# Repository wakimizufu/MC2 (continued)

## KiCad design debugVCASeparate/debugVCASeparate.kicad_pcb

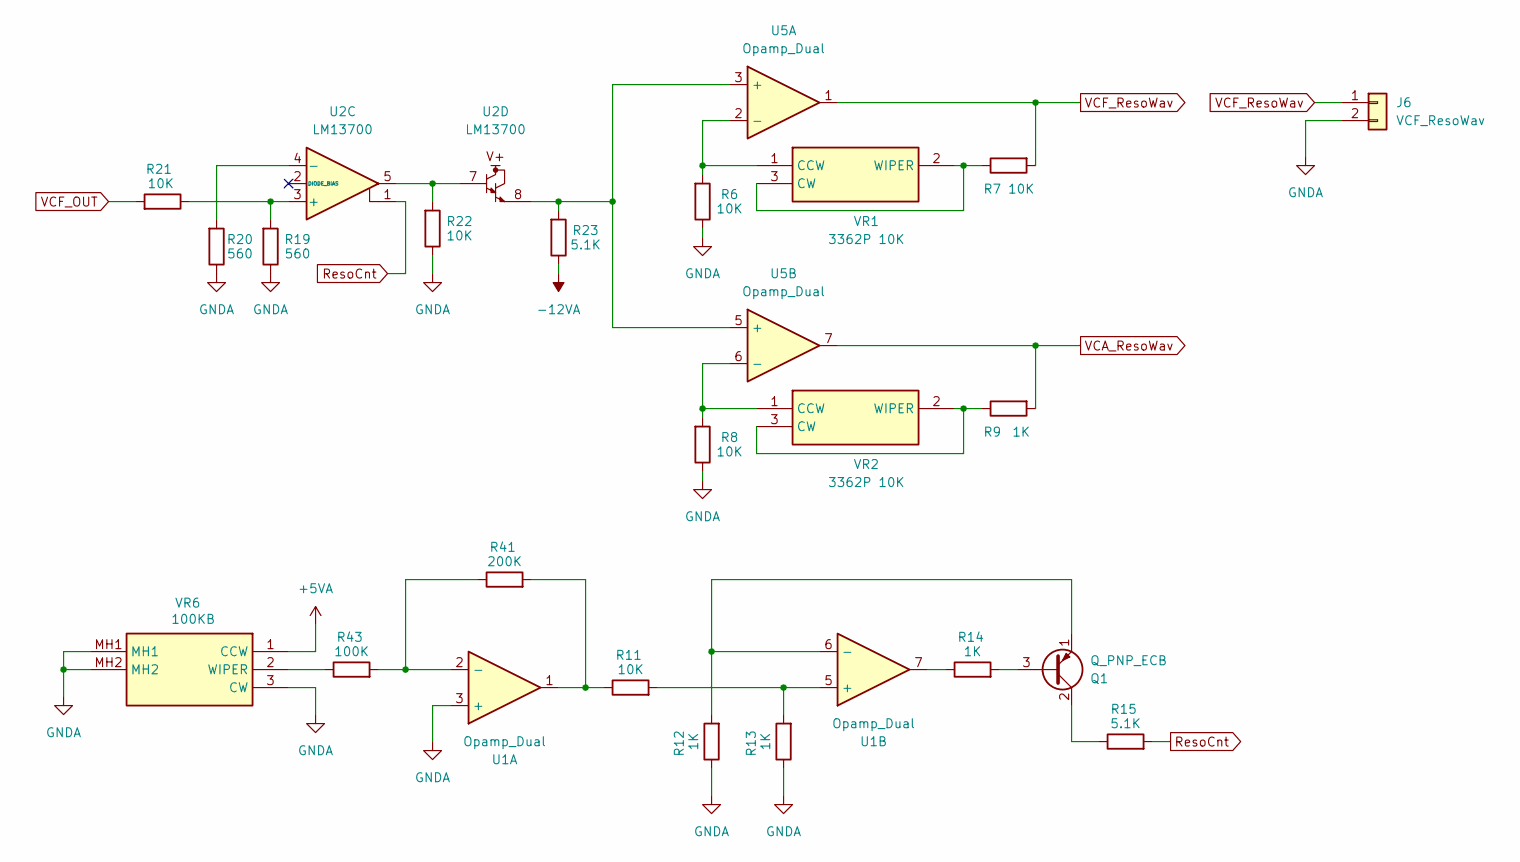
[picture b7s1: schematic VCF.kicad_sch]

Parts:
J6: VCF_ResoWav; PinSocket_1x02_P2.54mm_Vertical
Q1: Q_PNP_ECB; TO-92_HandSolder
R6, R7, R8, R11, R21, R22: 10K; R_Axial_DIN0204_L3.6mm_D1.6mm_P7.62mm_Horizontal
R9, R12, R13, R14: 1K; R_Axial_DIN0204_L3.6mm_D1.6mm_P7.62mm_Horizontal
R15, R23: 5.1K; R_Axial_DIN0204_L3.6mm_D1.6mm_P7.62mm_Horizontal
R19, R20: 560; R_Axial_DIN0204_L3.6mm_D1.6mm_P7.62mm_Horizontal
R41: 200K; R_Axial_DIN0204_L3.6mm_D1.6mm_P7.62mm_Horizontal
R43: 100K; R_Axial_DIN0204_L3.6mm_D1.6mm_P7.62mm_Horizontal
U1: Opamp_Dual; DIP-8_W7.62mm_LongPads
U2: LM13700; DIP-16_W7.62mm_LongPads
U5: Opamp_Dual; DIP-8_W7.62mm_Socket_LongPads
VR1, VR2: 3362P 10K; 3362P_1; Manufacturer_Part_Number 3362P-1-103LF; Mouser Part Number 652-3362P-1-103LF
VR6: 100KB; RK09D117000B; Manufacturer_Part_Number RK09D117000B; Mouser Part Number 688-RK09D117000B

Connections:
+5VA: VR6.1 (CCW); also elsewhere on the board
-12VA: R23.1; also elsewhere on the board
GNDA: J6.2, R6.1, R8.1, R12.1, R13.1, R19.1, R20.1, R22.1, U1.3 (+), VR6.3 (CW), VR6.MH1, VR6.MH2; also elsewhere on the board
unnamed: Q1.3 (B), R14.2
unnamed: Q1.2 (C), R15.1
unnamed: Q1.1 (E), R12.2, U1.6 (-)
unnamed: R11.1, R41.2, U1.1
unnamed: R14.1, U1.7
unnamed: R22.2, U2.5, U2.7
unnamed: R41.1, R43.2, U1.2 (-)
unnamed: R11.2, R13.2, U1.5 (+)
unnamed: R19.2, R21.1, U2.3 (+)
unnamed: R20.2, U2.4 (-)
unnamed: R23.2, U2.8, U5.3 (+), U5.5 (+)
unnamed: R6.2, U5.2 (-), VR1.1 (CCW)
unnamed: R8.2, U5.6 (-), VR2.1 (CCW)
unnamed: R7.1, VR1.2 (WIPER), VR1.3 (CW)
unnamed: R9.1, VR2.2 (WIPER), VR2.3 (CW)
unnamed: R43.1, VR6.2 (WIPER)
ResoCnt: R15.2, U2.1
VCA_ResoWav: R9.2, U5.7; also elsewhere on the board
VCF_OUT: R21.2; also elsewhere on the board
VCF_ResoWav: J6.1, R7.2, U5.1

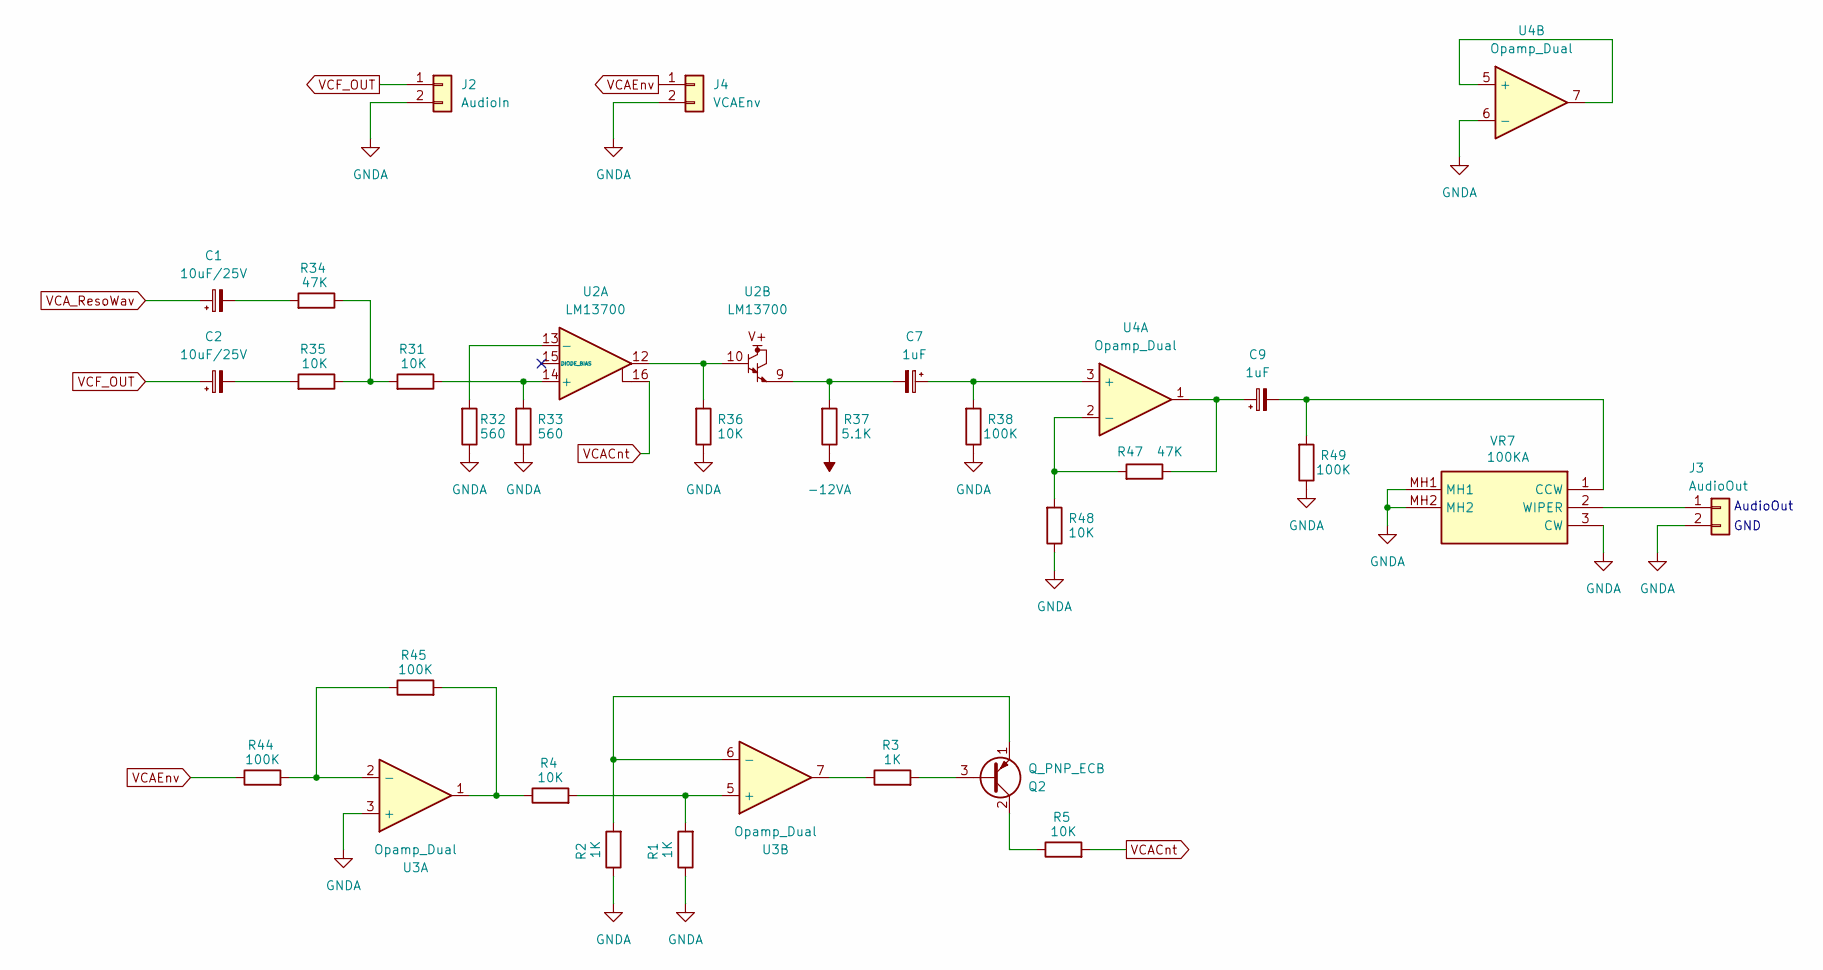
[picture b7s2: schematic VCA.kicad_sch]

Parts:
C1, C2: 10uF/25V; CP_Radial_D5.0mm_P2.50mm
C7, C9: 1uF; CP_Radial_D5.0mm_P2.50mm
J2: AudioIn; PinSocket_1x02_P2.54mm_Vertical
J3: AudioOut; PinHeader_1x02_P2.54mm_Vertical
J4: VCAEnv; PinSocket_1x02_P2.54mm_Vertical
Q2: Q_PNP_ECB; TO-92_HandSolder
R1, R2, R3: 1K; R_Axial_DIN0204_L3.6mm_D1.6mm_P7.62mm_Horizontal
R4, R5, R31, R35, R36, R48: 10K; R_Axial_DIN0204_L3.6mm_D1.6mm_P7.62mm_Horizontal
R32, R33: 560; R_Axial_DIN0204_L3.6mm_D1.6mm_P7.62mm_Horizontal
R34, R47: 47K; R_Axial_DIN0204_L3.6mm_D1.6mm_P7.62mm_Horizontal
R37: 5.1K; R_Axial_DIN0204_L3.6mm_D1.6mm_P7.62mm_Horizontal
R38, R44, R45, R49: 100K; R_Axial_DIN0204_L3.6mm_D1.6mm_P7.62mm_Horizontal
U2: LM13700; DIP-16_W7.62mm_LongPads
U3: Opamp_Dual; DIP-8_W7.62mm_LongPads
U4: Opamp_Dual; DIP-8_W7.62mm_Socket_LongPads
VR7: 100KA; RK09D117000B; Manufacturer_Part_Number RK09D117000B; Mouser Part Number 688-RK09D117000B

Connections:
-12VA: R37.1; also elsewhere on the board
GNDA: J2.2, J3.2, J4.2, R1.1, R2.1, R32.1, R33.1, R36.1, R38.1, R48.1, R49.1, U3.3 (+), U4.6 (-), VR7.3 (CW), VR7.MH1, VR7.MH2; also elsewhere on the board
unnamed: C1.2, R34.2
unnamed: C2.2, R35.2
unnamed: C7.2, R37.2, U2.9
unnamed: C9.1, R47.1, U4.1
unnamed: J3.1, VR7.2 (WIPER)
unnamed: Q2.3 (B), R3.2
unnamed: Q2.2 (C), R5.1
unnamed: Q2.1 (E), R2.2, U3.6 (-)
unnamed: R3.1, U3.7
unnamed: R4.1, R45.2, U3.1
unnamed: R31.2, R34.1, R35.1
unnamed: R36.2, U2.10, U2.12
unnamed: R31.1, R33.2, U2.14 (+)
unnamed: R32.2, U2.13 (-)
unnamed: R44.2, R45.1, U3.2 (-)
unnamed: R1.2, R4.2, U3.5 (+)
unnamed: C7.1, R38.2, U4.3 (+)
unnamed: R47.2, R48.2, U4.2 (-)
unnamed: U4.5 (+), U4.7
unnamed: C9.2, R49.2, VR7.1 (CCW)
VCACnt: R5.2, U2.16
VCAEnv: J4.1, R44.1
VCA_ResoWav: C1.1; also elsewhere on the board
VCF_OUT: C2.1, J2.1; also elsewhere on the board

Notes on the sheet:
GND
AudioOut

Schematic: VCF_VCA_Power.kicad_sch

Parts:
J1, J5: A_Power; PinHeader_1x06_P2.54mm_Vertical
U1, U3: Opamp_Dual; DIP-8_W7.62mm_LongPads
U2: LM13700; DIP-16_W7.62mm_LongPads
U4, U5: Opamp_Dual; DIP-8_W7.62mm_Socket_LongPads

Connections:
+5VA: J1.2, J5.2; also elsewhere on the board
+12VA: J1.1, J5.1, U1.8 (V+), U2.11 (V+), U3.8 (V+), U4.8 (V+), U5.8 (V+)
-5VA: J1.3, J5.3
-12VA: J1.4, J5.4, U1.4 (V-), U2.6 (V-), U3.4 (V-), U4.4 (V-), U5.4 (V-); also elsewhere on the board
GNDA: J1.6, J5.6; also elsewhere on the board

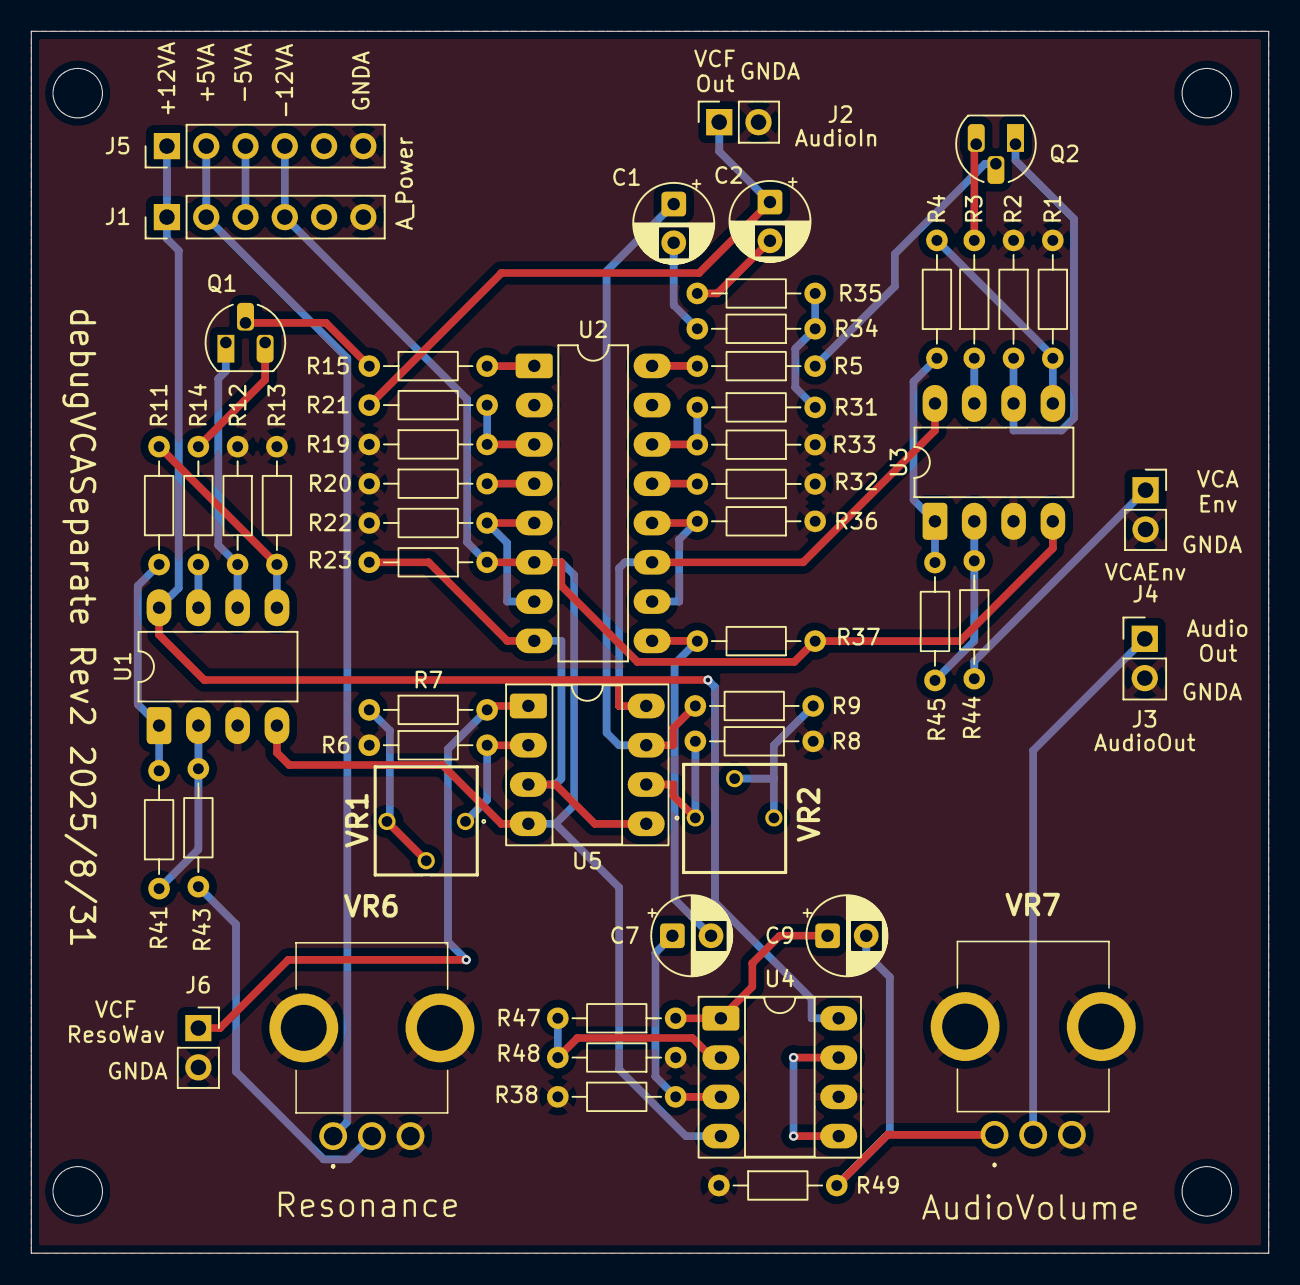
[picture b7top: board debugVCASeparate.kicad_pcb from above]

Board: 2 copper layers, 80.0 x 79.0 mm, 55 parts (0 on the bottom side), 47 nets.

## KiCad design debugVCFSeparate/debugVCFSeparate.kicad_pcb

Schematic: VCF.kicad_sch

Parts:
C1, C2, C3, C4: 250pF; C_Disc_D4.7mm_W2.5mm_P5.00mm
C8: 10uF BP; C_Radial_D5.0mm_H5.0mm_P2.00mm
J3: InResoWav; PinHeader_2x03_P2.54mm_Vertical
J4: FltOrder; PinSocket_1x03_P2.54mm_Vertical
J5: VCFOut; PinHeader_1x02_P2.54mm_Vertical
R1, R2, R7, R8, R12, R13, R17, R18: 560; R_Axial_DIN0204_L3.6mm_D1.6mm_P7.62mm_Horizontal
R3, R9, R14, R24: 68K; R_Axial_DIN0204_L3.6mm_D1.6mm_P7.62mm_Horizontal
R4, R5, R11, R16, R31: 100K; R_Axial_DIN0204_L3.6mm_D1.6mm_P7.62mm_Horizontal
R6, R10, R15, R30: 10K; R_Axial_DIN0204_L3.6mm_D1.6mm_P7.62mm_Horizontal
U1, U2: LM13700; DIP-16_W7.62mm_Socket_LongPads

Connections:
1stCap: C1.2, J3.4
1st_In_-: J3.3, R31.1
-12VA: R6.1, R10.1, R15.1, R30.1; also elsewhere on the board
GNDA: C2.2, C3.2, C4.2, J3.6, J5.2, R1.1, R2.1, R7.1, R8.1, R12.1, R13.1, R17.1, R18.1; also elsewhere on the board
LP6db: J4.1, R3.2, R5.1, R6.2, U1.9
LP12db: J4.2, R9.2, R10.2, R11.1, U1.8
LP18db: J4.3, R14.2, R15.2, R16.1, U2.9
unnamed: C1.1, U1.10, U1.12
unnamed: C2.1, U1.5, U1.7
unnamed: C3.1, U2.10, U2.12
unnamed: C4.1, U2.5, U2.7
unnamed: C8.2, R4.1
unnamed: R2.2, R4.2, U1.14 (+)
unnamed: R1.2, R3.1, R31.2, U1.13 (-)
unnamed: R5.2, R8.2, U1.3 (+)
unnamed: R7.2, R9.1, U1.4 (-)
unnamed: R11.2, R13.2, U2.14 (+)
unnamed: R12.2, R14.1, U2.13 (-)
unnamed: R16.2, R18.2, U2.3 (+)
unnamed: R17.2, R24.1, U2.4 (-)
ResoWav: J3.2, J3.5; also elsewhere on the board
VCFCnt: U1.1, U1.16, U2.1, U2.16; also elsewhere on the board
VCF_IN: C8.1; also elsewhere on the board
VCF_OUT: J5.1, R24.2, R30.2, U2.8

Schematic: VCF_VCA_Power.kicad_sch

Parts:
J1: A_Power; PinHeader_1x06_P2.54mm_Vertical
U1, U2: LM13700; DIP-16_W7.62mm_Socket_LongPads
U3: Opamp_Dual; DIP-8_W7.62mm_Socket_LongPads

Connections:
+5VA: J1.2; also elsewhere on the board
+12VA: J1.1, U1.11 (V+), U2.11 (V+), U3.8 (V+); also elsewhere on the board
-5VA: J1.3
-12VA: J1.4, U1.6 (V-), U2.6 (V-), U3.4 (V-); also elsewhere on the board
GNDA: J1.6; also elsewhere on the board

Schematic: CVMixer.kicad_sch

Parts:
J2: Input; PinSocket_2x06_P2.54mm_Vertical
Q1, Q2: Q_PNP_ECB; TO-92_HandSolder
Q4: Q_NPN_ECB; TO-92_HandSolder
R19: 27K; R_Axial_DIN0204_L3.6mm_D1.6mm_P7.62mm_Horizontal
R20: 100K; R_Axial_DIN0204_L3.6mm_D1.6mm_P7.62mm_Horizontal
R21: 1K; R_Axial_DIN0204_L3.6mm_D1.6mm_P7.62mm_Horizontal
R22: 47K; R_Axial_DIN0204_L3.6mm_D1.6mm_P7.62mm_Horizontal
R23, R39: 10K; R_Axial_DIN0204_L3.6mm_D1.6mm_P7.62mm_Horizontal
R25: 56K; R_Axial_DIN0204_L3.6mm_D1.6mm_P7.62mm_Horizontal
R26: 39K; R_Axial_DIN0204_L3.6mm_D1.6mm_P7.62mm_Horizontal
R27: 20K; R_Axial_DIN0204_L3.6mm_D1.6mm_P7.62mm_Horizontal
R28: 33K; R_Axial_DIN0204_L3.6mm_D1.6mm_P7.62mm_Horizontal
R29: 150K; R_Axial_DIN0204_L3.6mm_D1.6mm_P7.62mm_Horizontal
RV1: 3362P 100K; Potentiometer_Bourns_3386P_Vertical
RV2: 3362P 50K; Potentiometer_Bourns_3386P_Vertical
U3: Opamp_Dual; DIP-8_W7.62mm_Socket_LongPads
VR1, VR2, VR4: 100KB; RK09D117000B; Manufacturer_Part_Number RK09D117000B; Mouser Part Number 688-RK09D117000B
VR3: 100KA; RK09D117000B; Manufacturer_Part_Number RK09D117000B; Mouser Part Number 688-RK09D117000B

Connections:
+5VA: VR1.1 (CCW); also elsewhere on the board
+12VA: Q4.2 (C), R28.2, RV1.1; also elsewhere on the board
-12VA: R20.1, RV1.3; also elsewhere on the board
CV: J2.7, J2.8, RV2.2, RV2.3
FilterEnv: J2.3, J2.4, VR2.1 (CCW)
GNDA: J2.11, J2.12, Q1.2 (C), Q2.1 (E), R21.1, U3.2 (-), U3.5 (+), VR1.3 (CW), VR1.MH1, VR1.MH2, VR2.3 (CW), VR2.MH1, VR2.MH2, VR3.3 (CW), VR3.MH1, VR3.MH2, VR4.3 (CW), VR4.MH1, VR4.MH2; also elsewhere on the board
LFOSine: J2.5, J2.6, VR3.1 (CCW)
unnamed: Q1.3 (B), VR4.2 (WIPER)
unnamed: Q1.1 (E), R28.1, R29.1
unnamed: Q2.3 (B), Q4.1 (E), R20.2
unnamed: Q2.2 (C), R23.1
unnamed: Q4.3 (B), R19.2, R21.2, R22.2
unnamed: R19.1, R39.2, U3.7
unnamed: R22.1, RV1.2
unnamed: U3.1, U3.3 (+)
unnamed: R25.2, R26.2, R27.2, R29.2, R39.1, U3.6 (-)
unnamed: R27.1, VR1.2 (WIPER)
unnamed: R25.1, VR2.2 (WIPER)
unnamed: R26.1, VR3.2 (WIPER)
unnamed: RV2.1, VR4.1 (CCW)
ResoWav: J2.9, J2.10; also elsewhere on the board
VCFCnt: R23.2; also elsewhere on the board
VCF_IN: J2.1, J2.2; also elsewhere on the board

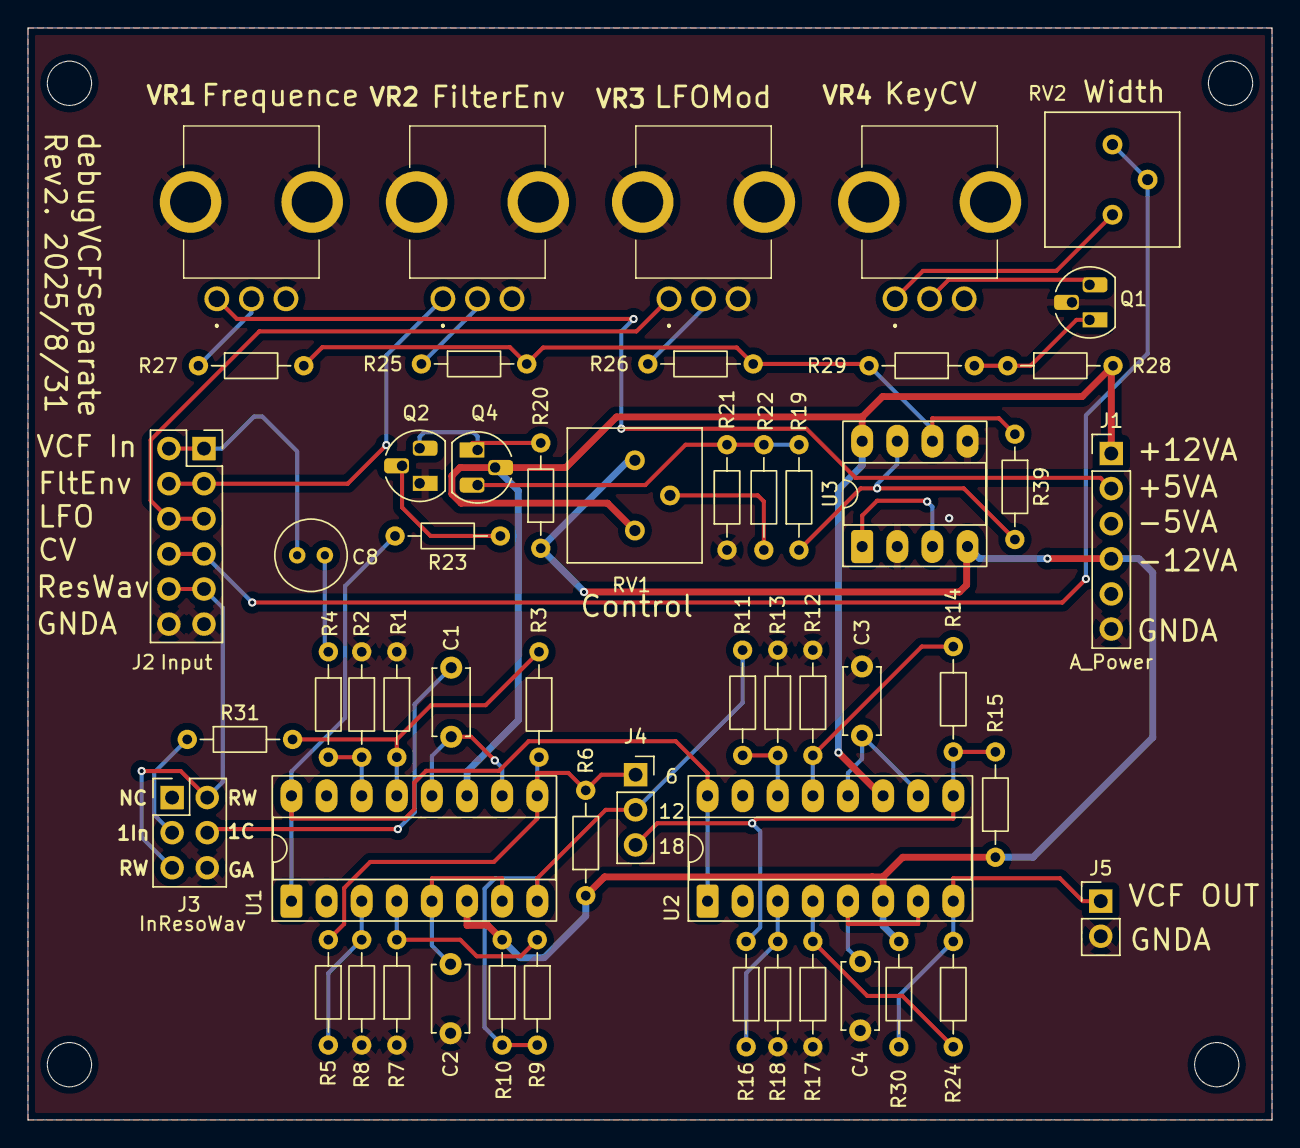
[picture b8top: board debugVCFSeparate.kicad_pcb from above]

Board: 2 copper layers, 90.0 x 79.0 mm, 54 parts (0 on the bottom side), 42 nets.

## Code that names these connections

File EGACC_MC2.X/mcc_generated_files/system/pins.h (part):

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// get/set IO_RA4 aliases
#define PWMFlt_TRIS                 TRISAbits.TRISA4
#define PWMFlt_LAT                  LATAbits.LATA4
#define PWMFlt_PORT                 PORTAbits.RA4
#define PWMFlt_WPU                  WPUAbits.WPUA4
#define PWMFlt_OD                   ODCONAbits.ODCA4
#define PWMFlt_ANS                  ANSELAbits.ANSA4
#define PWMFlt_SetHigh()            do { LATAbits.LATA4 = 1; } while(0)
#define PWMFlt_SetLow()             do { LATAbits.LATA4 = 0; } while(0)
#define PWMFlt_Toggle()             do { LATAbits.LATA4 = ~LATAbits.LATA4; } while(0)
#define PWMFlt_GetValue()           PORTAbits.RA4
#define PWMFlt_SetDigitalInput()    do { TRISAbits.TRISA4 = 1; } while(0)
#define PWMFlt_SetDigitalOutput()   do { TRISAbits.TRISA4 = 0; } while(0)
#define PWMFlt_SetPullup()          do { WPUAbits.WPUA4 = 1; } while(0)
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// get/set IO_RB4 aliases
#define accFlt_TRIS                 TRISBbits.TRISB4
#define accFlt_LAT                  LATBbits.LATB4
#define accFlt_PORT                 PORTBbits.RB4
#define accFlt_WPU                  WPUBbits.WPUB4
#define accFlt_OD                   ODCONBbits.ODCB4
#define accFlt_ANS                  ANSELBbits.ANSB4
#define accFlt_SetHigh()            do { LATBbits.LATB4 = 1; } while(0)
#define accFlt_SetLow()             do { LATBbits.LATB4 = 0; } while(0)
#define accFlt_Toggle()             do { LATBbits.LATB4 = ~LATBbits.LATB4; } while(0)
#define accFlt_GetValue()           PORTBbits.RB4
#define accFlt_SetDigitalInput()    do { TRISBbits.TRISB4 = 1; } while(0)
#define accFlt_SetDigitalOutput()   do { TRISBbits.TRISB4 = 0; } while(0)
#define accFlt_SetPullup()          do { WPUBbits.WPUB4 = 1; } while(0)
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// get/set IO_RB5 aliases
#define accAmp_TRIS                 TRISBbits.TRISB5
#define accAmp_LAT                  LATBbits.LATB5
#define accAmp_PORT                 PORTBbits.RB5
#define accAmp_WPU                  WPUBbits.WPUB5
#define accAmp_OD                   ODCONBbits.ODCB5
#define accAmp_ANS                  ANSELBbits.ANSB5
#define accAmp_SetHigh()            do { LATBbits.LATB5 = 1; } while(0)
#define accAmp_SetLow()             do { LATBbits.LATB5 = 0; } while(0)
#define accAmp_Toggle()             do { LATBbits.LATB5 = ~LATBbits.LATB5; } while(0)
#define accAmp_GetValue()           PORTBbits.RB5
#define accAmp_SetDigitalInput()    do { TRISBbits.TRISB5 = 1; } while(0)
#define accAmp_SetDigitalOutput()   do { TRISBbits.TRISB5 = 0; } while(0)
#define accAmp_SetPullup()          do { WPUBbits.WPUB5 = 1; } while(0)
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// get/set IO_RB6 aliases
#define Gate_TRIS                 TRISBbits.TRISB6
#define Gate_LAT                  LATBbits.LATB6
#define Gate_PORT                 PORTBbits.RB6
#define Gate_WPU                  WPUBbits.WPUB6
#define Gate_OD                   ODCONBbits.ODCB6
#define Gate_ANS                  ANSELBbits.ANSB6
#define Gate_SetHigh()            do { LATBbits.LATB6 = 1; } while(0)
#define Gate_SetLow()             do { LATBbits.LATB6 = 0; } while(0)
#define Gate_Toggle()             do { LATBbits.LATB6 = ~LATBbits.LATB6; } while(0)
#define Gate_GetValue()           PORTBbits.RB6
#define Gate_SetDigitalInput()    do { TRISBbits.TRISB6 = 1; } while(0)
#define Gate_SetDigitalOutput()   do { TRISBbits.TRISB6 = 0; } while(0)
#define Gate_SetPullup()          do { WPUBbits.WPUB6 = 1; } while(0)
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// get/set IO_RB7 aliases
#define Release_TRIS                 TRISBbits.TRISB7
#define Release_LAT                  LATBbits.LATB7
#define Release_PORT                 PORTBbits.RB7
#define Release_WPU                  WPUBbits.WPUB7
#define Release_OD                   ODCONBbits.ODCB7
#define Release_ANS                  ANSELBbits.ANSB7
#define Release_SetHigh()            do { LATBbits.LATB7 = 1; } while(0)
#define Release_SetLow()             do { LATBbits.LATB7 = 0; } while(0)
#define Release_Toggle()             do { LATBbits.LATB7 = ~LATBbits.LATB7; } while(0)
#define Release_GetValue()           PORTBbits.RB7
#define Release_SetDigitalInput()    do { TRISBbits.TRISB7 = 1; } while(0)
#define Release_SetDigitalOutput()   do { TRISBbits.TRISB7 = 0; } while(0)
#define Release_SetPullup()          do { WPUBbits.WPUB7 = 1; } while(0)
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// get/set IO_RC1 aliases
#define PWMAmp_TRIS                 TRISCbits.TRISC1
#define PWMAmp_LAT                  LATCbits.LATC1
#define PWMAmp_PORT                 PORTCbits.RC1
#define PWMAmp_WPU                  WPUCbits.WPUC1
#define PWMAmp_OD                   ODCONCbits.ODCC1
#define PWMAmp_ANS                  ANSELCbits.ANSC1
#define PWMAmp_SetHigh()            do { LATCbits.LATC1 = 1; } while(0)
#define PWMAmp_SetLow()             do { LATCbits.LATC1 = 0; } while(0)
#define PWMAmp_Toggle()             do { LATCbits.LATC1 = ~LATCbits.LATC1; } while(0)
#define PWMAmp_GetValue()           PORTCbits.RC1
#define PWMAmp_SetDigitalInput()    do { TRISCbits.TRISC1 = 1; } while(0)
#define PWMAmp_SetDigitalOutput()   do { TRISCbits.TRISC1 = 0; } while(0)
#define PWMAmp_SetPullup()          do { WPUCbits.WPUC1 = 1; } while(0)
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// get/set IO_RC2 aliases
#define AmpWave_TRIS                 TRISCbits.TRISC2
#define AmpWave_LAT                  LATCbits.LATC2
#define AmpWave_PORT                 PORTCbits.RC2
#define AmpWave_WPU                  WPUCbits.WPUC2
#define AmpWave_OD                   ODCONCbits.ODCC2
#define AmpWave_ANS                  ANSELCbits.ANSC2
#define AmpWave_SetHigh()            do { LATCbits.LATC2 = 1; } while(0)
#define AmpWave_SetLow()             do { LATCbits.LATC2 = 0; } while(0)
#define AmpWave_Toggle()             do { LATCbits.LATC2 = ~LATCbits.LATC2; } while(0)
#define AmpWave_GetValue()           PORTCbits.RC2
#define AmpWave_SetDigitalInput()    do { TRISCbits.TRISC2 = 1; } while(0)
#define AmpWave_SetDigitalOutput()   do { TRISCbits.TRISC2 = 0; } while(0)
#define AmpWave_SetPullup()          do { WPUCbits.WPUC2 = 1; } while(0)
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// get/set IO_RC3 aliases
#define Attack_TRIS                 TRISCbits.TRISC3
#define Attack_LAT                  LATCbits.LATC3
#define Attack_PORT                 PORTCbits.RC3
#define Attack_WPU                  WPUCbits.WPUC3
#define Attack_OD                   ODCONCbits.ODCC3
#define Attack_ANS                  ANSELCbits.ANSC3
#define Attack_SetHigh()            do { LATCbits.LATC3 = 1; } while(0)
#define Attack_SetLow()             do { LATCbits.LATC3 = 0; } while(0)
#define Attack_Toggle()             do { LATCbits.LATC3 = ~LATCbits.LATC3; } while(0)
#define Attack_GetValue()           PORTCbits.RC3
#define Attack_SetDigitalInput()    do { TRISCbits.TRISC3 = 1; } while(0)
#define Attack_SetDigitalOutput()   do { TRISCbits.TRISC3 = 0; } while(0)
#define Attack_SetPullup()          do { WPUCbits.WPUC3 = 1; } while(0)
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// get/set IO_RC4 aliases
#define AccLv_TRIS                 TRISCbits.TRISC4
#define AccLv_LAT                  LATCbits.LATC4
#define AccLv_PORT                 PORTCbits.RC4
#define AccLv_WPU                  WPUCbits.WPUC4
#define AccLv_OD                   ODCONCbits.ODCC4
#define AccLv_ANS                  ANSELCbits.ANSC4
#define AccLv_SetHigh()            do { LATCbits.LATC4 = 1; } while(0)
#define AccLv_SetLow()             do { LATCbits.LATC4 = 0; } while(0)
#define AccLv_Toggle()             do { LATCbits.LATC4 = ~LATCbits.LATC4; } while(0)
#define AccLv_GetValue()           PORTCbits.RC4
#define AccLv_SetDigitalInput()    do { TRISCbits.TRISC4 = 1; } while(0)
#define AccLv_SetDigitalOutput()   do { TRISCbits.TRISC4 = 0; } while(0)
#define AccLv_SetPullup()          do { WPUCbits.WPUC4 = 1; } while(0)
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// get/set IO_RC6 aliases
#define Decay_TRIS                 TRISCbits.TRISC6
#define Decay_LAT                  LATCbits.LATC6
#define Decay_PORT                 PORTCbits.RC6
#define Decay_WPU                  WPUCbits.WPUC6
#define Decay_OD                   ODCONCbits.ODCC6
#define Decay_ANS                  ANSELCbits.ANSC6
#define Decay_SetHigh()            do { LATCbits.LATC6 = 1; } while(0)
#define Decay_SetLow()             do { LATCbits.LATC6 = 0; } while(0)
#define Decay_Toggle()             do { LATCbits.LATC6 = ~LATCbits.LATC6; } while(0)
#define Decay_GetValue()           PORTCbits.RC6
#define Decay_SetDigitalInput()    do { TRISCbits.TRISC6 = 1; } while(0)
#define Decay_SetDigitalOutput()   do { TRISCbits.TRISC6 = 0; } while(0)
#define Decay_SetPullup()          do { WPUCbits.WPUC6 = 1; } while(0)
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// get/set IO_RC7 aliases
#define Sustain_TRIS                 TRISCbits.TRISC7
#define Sustain_LAT                  LATCbits.LATC7
#define Sustain_PORT                 PORTCbits.RC7
#define Sustain_WPU                  WPUCbits.WPUC7
#define Sustain_OD                   ODCONCbits.ODCC7
#define Sustain_ANS                  ANSELCbits.ANSC7
#define Sustain_SetHigh()            do { LATCbits.LATC7 = 1; } while(0)
#define Sustain_SetLow()             do { LATCbits.LATC7 = 0; } while(0)
#define Sustain_Toggle()             do { LATCbits.LATC7 = ~LATCbits.LATC7; } while(0)
#define Sustain_GetValue()           PORTCbits.RC7
#define Sustain_SetDigitalInput()    do { TRISCbits.TRISC7 = 1; } while(0)
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
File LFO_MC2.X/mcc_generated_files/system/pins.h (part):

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// get/set IO_RA2 aliases
#define Test_TRIS                 TRISAbits.TRISA2
#define Test_LAT                  LATAbits.LATA2
#define Test_PORT                 PORTAbits.RA2
#define Test_WPU                  WPUAbits.WPUA2
#define Test_OD                   ODCONAbits.ODCA2
#define Test_ANS                  ANSELAbits.ANSA2
#define Test_SetHigh()            do { LATAbits.LATA2 = 1; } while(0)
#define Test_SetLow()             do { LATAbits.LATA2 = 0; } while(0)
#define Test_Toggle()             do { LATAbits.LATA2 = ~LATAbits.LATA2; } while(0)
#define Test_GetValue()           PORTAbits.RA2
#define Test_SetDigitalInput()    do { TRISAbits.TRISA2 = 1; } while(0)
#define Test_SetDigitalOutput()   do { TRISAbits.TRISA2 = 0; } while(0)
#define Test_SetPullup()          do { WPUAbits.WPUA2 = 1; } while(0)
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// get/set IO_RA4 aliases
#define RndSeed_TRIS                 TRISAbits.TRISA4
#define RndSeed_LAT                  LATAbits.LATA4
#define RndSeed_PORT                 PORTAbits.RA4
#define RndSeed_WPU                  WPUAbits.WPUA4
#define RndSeed_OD                   ODCONAbits.ODCA4
#define RndSeed_ANS                  ANSELAbits.ANSA4
#define RndSeed_SetHigh()            do { LATAbits.LATA4 = 1; } while(0)
#define RndSeed_SetLow()             do { LATAbits.LATA4 = 0; } while(0)
#define RndSeed_Toggle()             do { LATAbits.LATA4 = ~LATAbits.LATA4; } while(0)
#define RndSeed_GetValue()           PORTAbits.RA4
#define RndSeed_SetDigitalInput()    do { TRISAbits.TRISA4 = 1; } while(0)
#define RndSeed_SetDigitalOutput()   do { TRISAbits.TRISA4 = 0; } while(0)
#define RndSeed_SetPullup()          do { WPUAbits.WPUA4 = 1; } while(0)
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// get/set IO_RA5 aliases
#define Square_TRIS                 TRISAbits.TRISA5
#define Square_LAT                  LATAbits.LATA5
#define Square_PORT                 PORTAbits.RA5
#define Square_WPU                  WPUAbits.WPUA5
#define Square_OD                   ODCONAbits.ODCA5
#define Square_ANS                  ANSELAbits.ANSA5
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// get/set IO_RC0 aliases
#define Gate_TRIS                 TRISCbits.TRISC0
#define Gate_LAT                  LATCbits.LATC0
#define Gate_PORT                 PORTCbits.RC0
#define Gate_WPU                  WPUCbits.WPUC0
#define Gate_OD                   ODCONCbits.ODCC0
#define Gate_ANS                  ANSELCbits.ANSC0
#define Gate_SetHigh()            do { LATCbits.LATC0 = 1; } while(0)
#define Gate_SetLow()             do { LATCbits.LATC0 = 0; } while(0)
#define Gate_Toggle()             do { LATCbits.LATC0 = ~LATCbits.LATC0; } while(0)
#define Gate_GetValue()           PORTCbits.RC0
#define Gate_SetDigitalInput()    do { TRISCbits.TRISC0 = 1; } while(0)
#define Gate_SetDigitalOutput()   do { TRISCbits.TRISC0 = 0; } while(0)
#define Gate_SetPullup()          do { WPUCbits.WPUC0 = 1; } while(0)
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// get/set IO_RC1 aliases
#define Rate_TRIS                 TRISCbits.TRISC1
#define Rate_LAT                  LATCbits.LATC1
#define Rate_PORT                 PORTCbits.RC1
#define Rate_WPU                  WPUCbits.WPUC1
#define Rate_OD                   ODCONCbits.ODCC1
#define Rate_ANS                  ANSELCbits.ANSC1
#define Rate_SetHigh()            do { LATCbits.LATC1 = 1; } while(0)
#define Rate_SetLow()             do { LATCbits.LATC1 = 0; } while(0)
#define Rate_Toggle()             do { LATCbits.LATC1 = ~LATCbits.LATC1; } while(0)
#define Rate_GetValue()           PORTCbits.RC1
#define Rate_SetDigitalInput()    do { TRISCbits.TRISC1 = 1; } while(0)
#define Rate_SetDigitalOutput()   do { TRISCbits.TRISC1 = 0; } while(0)
#define Rate_SetPullup()          do { WPUCbits.WPUC1 = 1; } while(0)
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// get/set IO_RC2 aliases
#define Decay_TRIS                 TRISCbits.TRISC2
#define Decay_LAT                  LATCbits.LATC2
#define Decay_PORT                 PORTCbits.RC2
#define Decay_WPU                  WPUCbits.WPUC2
#define Decay_OD                   ODCONCbits.ODCC2
#define Decay_ANS                  ANSELCbits.ANSC2
#define Decay_SetHigh()            do { LATCbits.LATC2 = 1; } while(0)
#define Decay_SetLow()             do { LATCbits.LATC2 = 0; } while(0)
#define Decay_Toggle()             do { LATCbits.LATC2 = ~LATCbits.LATC2; } while(0)
#define Decay_GetValue()           PORTCbits.RC2
#define Decay_SetDigitalInput()    do { TRISCbits.TRISC2 = 1; } while(0)
#define Decay_SetDigitalOutput()   do { TRISCbits.TRISC2 = 0; } while(0)
#define Decay_SetPullup()          do { WPUCbits.WPUC2 = 1; } while(0)
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// get/set IO_RC3 aliases
#define Randum_TRIS                 TRISCbits.TRISC3
#define Randum_LAT                  LATCbits.LATC3
#define Randum_PORT                 PORTCbits.RC3
#define Randum_WPU                  WPUCbits.WPUC3
#define Randum_OD                   ODCONCbits.ODCC3
#define Randum_ANS                  ANSELCbits.ANSC3
#define Randum_SetHigh()            do { LATCbits.LATC3 = 1; } while(0)
#define Randum_SetLow()             do { LATCbits.LATC3 = 0; } while(0)
#define Randum_Toggle()             do { LATCbits.LATC3 = ~LATCbits.LATC3; } while(0)
#define Randum_GetValue()           PORTCbits.RC3
#define Randum_SetDigitalInput()    do { TRISCbits.TRISC3 = 1; } while(0)
#define Randum_SetDigitalOutput()   do { TRISCbits.TRISC3 = 0; } while(0)
#define Randum_SetPullup()          do { WPUCbits.WPUC3 = 1; } while(0)
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// get/set IO_RC4 aliases
#define Triangle_TRIS                 TRISCbits.TRISC4
#define Triangle_LAT                  LATCbits.LATC4
#define Triangle_PORT                 PORTCbits.RC4
#define Triangle_WPU                  WPUCbits.WPUC4
#define Triangle_OD                   ODCONCbits.ODCC4
#define Triangle_ANS                  ANSELCbits.ANSC4
#define Triangle_SetHigh()            do { LATCbits.LATC4 = 1; } while(0)
#define Triangle_SetLow()             do { LATCbits.LATC4 = 0; } while(0)
#define Triangle_Toggle()             do { LATCbits.LATC4 = ~LATCbits.LATC4; } while(0)
#define Triangle_GetValue()           PORTCbits.RC4
#define Triangle_SetDigitalInput()    do { TRISCbits.TRISC4 = 1; } while(0)
#define Triangle_SetDigitalOutput()   do { TRISCbits.TRISC4 = 0; } while(0)
#define Triangle_SetPullup()          do { WPUCbits.WPUC4 = 1; } while(0)
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// get/set IO_RC5 aliases
#define Sine_TRIS                 TRISCbits.TRISC5
#define Sine_LAT                  LATCbits.LATC5
#define Sine_PORT                 PORTCbits.RC5
#define Sine_WPU                  WPUCbits.WPUC5
#define Sine_OD                   ODCONCbits.ODCC5
#define Sine_ANS                  ANSELCbits.ANSC5
#define Sine_SetHigh()            do { LATCbits.LATC5 = 1; } while(0)
#define Sine_SetLow()             do { LATCbits.LATC5 = 0; } while(0)
#define Sine_Toggle()             do { LATCbits.LATC5 = ~LATCbits.LATC5; } while(0)
#define Sine_GetValue()           PORTCbits.RC5
#define Sine_SetDigitalInput()    do { TRISCbits.TRISC5 = 1; } while(0)
#define Sine_SetDigitalOutput()   do { TRISCbits.TRISC5 = 0; } while(0)
#define Sine_SetPullup()          do { WPUCbits.WPUC5 = 1; } while(0)
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
/**
 * @ingroup  pinsdriver
 * @brief Interrupt on Change Handler for the Gate pin functionality
 * @param none
 * @return none
 */
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
/**
 * @ingroup  pinsdriver
 * @brief Interrupt Handler Setter for Gate pin interrupt-on-change functionality.
 *        Allows selecting an interrupt handler for Gate at application runtime.
 * @pre Pins intializer called
 * @param InterruptHandler function pointer.
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
/**
 * @ingroup  pinsdriver
 * @brief Dynamic Interrupt Handler for Gate pin.
 *        This is a dynamic interrupt handler to be used together with the Gate_SetInterruptHandler() method.
 *        This handler is called every time the Gate ISR is executed and allows any function to be registered at runtime.
 * @pre Pins intializer called
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
/**
 * @ingroup  pinsdriver
 * @brief Default Interrupt Handler for Gate pin. 
 *        This is a predefined interrupt handler to be used together with the Gate_SetInterruptHandler() method.
 *        This handler is called every time the Gate ISR is executed. 
 * @pre Pins intializer called
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
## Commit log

2025-06-10 MC2
    この時点のファイルを登録
2025-06-10 LFOSeparate
    アートワーク作成中
2025-06-11 LFOSeparate
    LFOSeparateは配線完了
    EGSeparateは回路図作成中
2025-06-12 EGSeparate
    配線完了 シルク未記入
2025-06-13 EGSeparate
    シルクスクリーンに説明文を追記
2025-06-15 MC2
    アクセントレベルを追加したEGACCを登録
    回路全般部品配置済
2025-06-16 VCFSeparater
    回路図作成中
2025-06-17 VCFSeparate
    レゾナンスVCAを追加
    コントローラー系を作成中
2025-06-25 MC2
    VCO,VCF+VCA,Powerを登録
2025-06-29 MC2
    ガーバーデータ出力
    BOMファイル出力
    NJM2374A関連プロジェクトを作成
    PowerSeparateが完了
2025-07-20 MC2
    基板製造依頼～Power.LFO検証完了まで
2025-07-20 LFOSeparate
    プログラムと回路のデバッグ後の修正を反映
2025-07-21 EGACC MC2
    プログラムと回路デバッグ後の修正を反映
2025-07-21 EGSeparater
    ~MCLRのリセット回路を追加
2025-08-16 MC2
    ここまででFIXした内容
2025-08-31 MC2
    デバッグ一通り完了して動作出来た
2025-09-07 MC2
    SynthBoard LFO+VCO とりあえずdebug状態を組み合わせた
2025-09-09 SynthBoard
    部品をSMDにしてVCO+LFOを配置した
2025-09-14 SynthBoard
    アナログのみ一通り設置 デジタルはなし
2025-09-14 SynthBorad
    デジタルも配置した
2025-09-15 SynthBoard_Left
    部品配置まで SWの極性確認待ちとする
2025-09-15 SynthBoard
    Rightを配置済
    Leftの配線ミスを修正
2025-09-15 SynthBoard Right
    配線ミスを修正
2025-09-21 SynthBoard_Left
    JLCPCBでBasic部品に置き換えた
2025-09-21 SynthBoard Right
    Basic部品で更新まで
2025-10-02 EGACC_MC2
    対数カーブの最大値(711)に合わせて修正
2025-10-04 EGACC_MC2
    通常時の対数カーブの開始位置が間違ってたので修正
    ADRの時間指定が間違ってたので修正
    アクセントの計算が間違ってたので修正
    一先ず仕様は満たしたはず
2025-10-05 LFO MC2
    Delay時間の指定ミスを修正
    一通り仕様を満たせるように修正完了
2026-02-22 MC2
    まとめて登録
2026-02-22 MC2 Synth-Board Rotary
    V0.2
    U10:PIn4 -12Vに接続
    IC4:Pin12,13 デフォルト12でジャンパーパッドを追加
    R86:三角波をS2に未接続だったのを修正
    S2,S3:スイッチ動作を上下入れ替え
    VR9:右に2.5mm移動に伴い周辺回路の配置を変更
2026-03-14 PowerAndJack
    一通り作成済
